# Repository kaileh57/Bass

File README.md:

This is a precision fender-style electric bass designed by me!

It's got three knobs for volume, treble and bass, as well as a custom PCB for active sound managment, and a dual amp system to play audio to EITHER a 1/4" jack OR a standard 3.5mm headphone jack. 
It also has a small rechargable battery to let me play with my headphones away from an amp or power source for hopefully a few hours at a time. 

The bass is pretty standard, and if you wanna 3d print the two parts, buy all the components, the wiring diagram should get you through the complex part!

I made this as I don't currently have an electric bass to play on, and would really like the chance to make my own instrument and start playing new types of music!

Here's what it looks like assembled:

The PCB

Wiring diagram:

The bom can be found in the bom.csv!

This was made (JUST IN TIME) for hack clubs blueprint program, which has been awesome!

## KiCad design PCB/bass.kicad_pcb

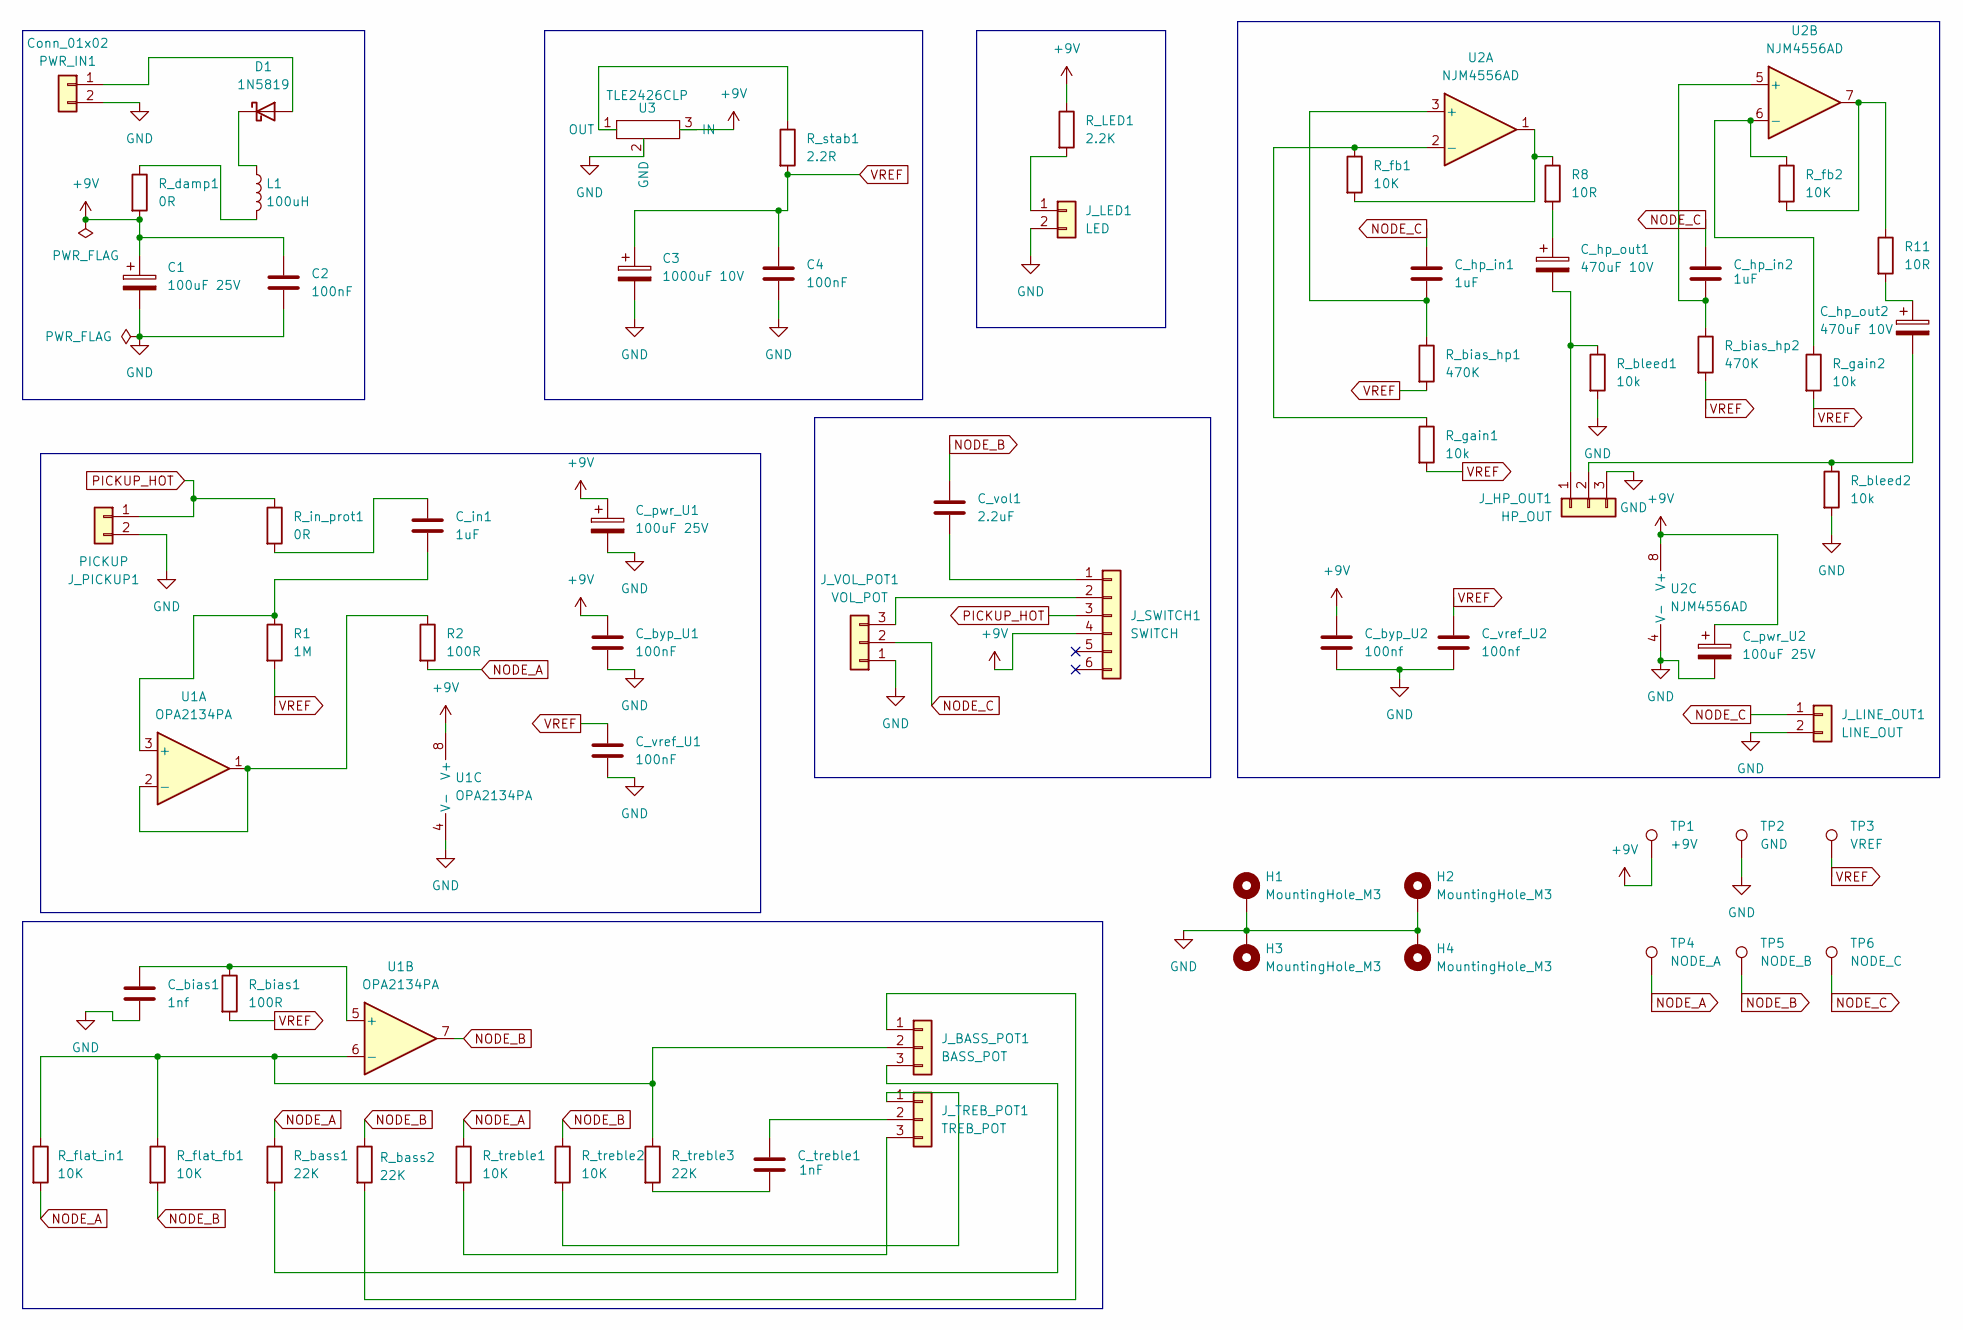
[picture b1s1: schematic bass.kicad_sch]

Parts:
C1: 100uF 25V; CP_Radial_D8.0mm_P3.50mm
C2, C4: 100nF; C_Disc_D5.0mm_W2.5mm_P5.00mm
C3: 1000uF 10V; CP_Radial_D12.5mm_P5.00mm
C_bias1: 1nf; C_Disc_D5.0mm_W2.5mm_P5.00mm
C_byp_U1: 100nF; C_Disc_D5.0mm_W2.5mm_P5.00mm
C_byp_U2: 100nf; C_Disc_D5.0mm_W2.5mm_P5.00mm
C_hp_in1, C_hp_in2: 1uF; C_Rect_L7.2mm_W2.5mm_P5.00mm_FKS2_FKP2_MKS2_MKP2
C_hp_out1, C_hp_out2: 470uF 10V; CP_Radial_D10.0mm_P5.00mm
C_in1: 1uF; C_Rect_L7.2mm_W2.5mm_P5.00mm_FKS2_FKP2_MKS2_MKP2
C_pwr_U1, C_pwr_U2: 100uF 25V; CP_Radial_D8.0mm_P3.50mm
C_treble1: 1nF; C_Rect_L7.2mm_W2.5mm_P5.00mm_FKS2_FKP2_MKS2_MKP2
C_vol1: 2.2uF; C_Rect_L13.5mm_W5.0mm_P10.00mm_FKS3_FKP3_MKS4
C_vref_U1: 100nF; C_Disc_D5.0mm_W2.5mm_P5.00mm
C_vref_U2: 100nf; C_Disc_D5.0mm_W2.5mm_P5.00mm
D1: 1N5819; D_DO-41_SOD81_P10.16mm_Horizontal
H1, H2, H3, H4: MountingHole_M3; MountingHole_3.2mm_M3_Pad
J_BASS_POT1: BASS_POT; PinHeader_1x03_P2.54mm_Vertical
J_HP_OUT1: HP_OUT; PinHeader_1x03_P2.54mm_Vertical
J_LED1: LED; PinHeader_1x02_P2.54mm_Vertical
J_LINE_OUT1: LINE_OUT; PinHeader_1x02_P2.54mm_Vertical
J_PICKUP1: PICKUP; PinHeader_1x02_P2.54mm_Vertical
J_SWITCH1: SWITCH; PinHeader_1x06_P2.54mm_Vertical
J_TREB_POT1: TREB_POT; PinHeader_1x03_P2.54mm_Vertical
J_VOL_POT1: VOL_POT; PinHeader_1x03_P2.54mm_Vertical
L1: 100uH; L_Radial_D10.0mm_P5.00mm_Fastron_07M
PWR_IN1: Conn_01x02; PinHeader_1x02_P2.54mm_Vertical
R1: 1M; R_Axial_DIN0207_L6.3mm_D2.5mm_P10.16mm_Horizontal
R2: 100R; R_Axial_DIN0207_L6.3mm_D2.5mm_P10.16mm_Horizontal
R8, R11: 10R; R_Axial_DIN0207_L6.3mm_D2.5mm_P10.16mm_Horizontal
R_LED1: 2.2K; R_Axial_DIN0207_L6.3mm_D2.5mm_P10.16mm_Horizontal
R_bass1, R_bass2: 22K; R_Axial_DIN0207_L6.3mm_D2.5mm_P10.16mm_Horizontal
R_bias1: 100R; R_Axial_DIN0207_L6.3mm_D2.5mm_P10.16mm_Horizontal
R_bias_hp1, R_bias_hp2: 470K; R_Axial_DIN0207_L6.3mm_D2.5mm_P10.16mm_Horizontal
R_bleed1, R_bleed2: 10k; R_Axial_DIN0207_L6.3mm_D2.5mm_P10.16mm_Horizontal
R_damp1: 0R; R_Axial_DIN0207_L6.3mm_D2.5mm_P10.16mm_Horizontal
R_fb1, R_fb2: 10K; R_Axial_DIN0207_L6.3mm_D2.5mm_P10.16mm_Horizontal
R_flat_fb1: 10K; R_Axial_DIN0207_L6.3mm_D2.5mm_P10.16mm_Horizontal
R_flat_in1: 10K; R_Axial_DIN0207_L6.3mm_D2.5mm_P10.16mm_Horizontal
R_gain1, R_gain2: 10k; R_Axial_DIN0207_L6.3mm_D2.5mm_P10.16mm_Horizontal
R_in_prot1: 0R; R_Axial_DIN0207_L6.3mm_D2.5mm_P10.16mm_Horizontal
R_stab1: 2.2R; R_Axial_DIN0207_L6.3mm_D2.5mm_P10.16mm_Horizontal
R_treble1, R_treble2: 10K; R_Axial_DIN0207_L6.3mm_D2.5mm_P10.16mm_Horizontal
R_treble3: 22K; R_Axial_DIN0207_L6.3mm_D2.5mm_P10.16mm_Horizontal
TP1: +9V; TestPoint_Pad_2.0x2.0mm
TP2: GND; TestPoint_Pad_2.0x2.0mm
TP3: VREF; TestPoint_Pad_2.0x2.0mm
TP4: NODE_A; TestPoint_Pad_2.0x2.0mm
TP5: NODE_B; TestPoint_Pad_2.0x2.0mm
TP6: NODE_C; TestPoint_Pad_2.0x2.0mm
U1: OPA2134PA; DIP-8_W7.62mm
U2: NJM4556AD; DIP-8_W7.62mm
U3: TLE2426CLP; TO-92_Inline

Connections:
+9V: C1.1, C2.1, C_byp_U1.1, C_byp_U2.1, C_pwr_U1.1, C_pwr_U2.1, J_SWITCH1.4, R_LED1.1, R_damp1.2, TP1.1, U1.8 (V+), U2.8 (V+), U3.3 (IN)
GND: C1.2, C2.2, C3.2, C4.2, C_bias1.2, C_byp_U1.2, C_byp_U2.2, C_pwr_U1.2, C_pwr_U2.2, C_vref_U1.2, C_vref_U2.2, H1.1, H2.1, H3.1, H4.1, J_HP_OUT1.3, J_LED1.2, J_LINE_OUT1.2, J_PICKUP1.2, J_VOL_POT1.1, PWR_IN1.2, R_bleed1.2, R_bleed2.2, TP2.1, U1.4 (V-), U2.4 (V-), U3.2 (GND)
NODE_A: R2.2, R_bass1.1, R_flat_in1.2, R_treble1.1, TP4.1
NODE_B: C_vol1.1, R_bass2.1, R_flat_fb1.2, R_treble2.1, TP5.1, U1.7
NODE_C: C_hp_in1.1, C_hp_in2.1, J_LINE_OUT1.1, J_VOL_POT1.2, TP6.1
unnamed: C_hp_out1.1, R8.2
unnamed: C_hp_out2.1, R11.2
unnamed: C_in1.1, R_in_prot1.2
unnamed: C_treble1.2, R_treble3.2
unnamed: D1.2 (A), PWR_IN1.1
unnamed: D1.1 (K), L1.1
unnamed: J_BASS_POT1.1, R_bass2.2
unnamed: J_BASS_POT1.2, R_flat_fb1.1, R_flat_in1.1, R_treble3.1, U1.6 (-)
unnamed: J_BASS_POT1.3, R_bass1.2
unnamed: C_hp_out1.2, J_HP_OUT1.1, R_bleed1.1
unnamed: C_hp_out2.2, J_HP_OUT1.2, R_bleed2.1
unnamed: J_LED1.1, R_LED1.2
unnamed: C_vol1.2, J_SWITCH1.1
unnamed: J_SWITCH1.2, J_VOL_POT1.3
unnamed: J_TREB_POT1.1, R_treble2.2
unnamed: C_treble1.1, J_TREB_POT1.2
unnamed: J_TREB_POT1.3, R_treble1.2
unnamed: L1.2, R_damp1.1
unnamed: R8.1, R_fb1.2, U2.1
unnamed: R11.1, R_fb2.2, U2.7
unnamed: C_in1.2, R1.1, U1.3 (+)
unnamed: R2.1, U1.1, U1.2 (-)
unnamed: C_bias1.1, R_bias1.1, U1.5 (+)
unnamed: C_hp_in1.2, R_bias_hp1.1, U2.3 (+)
unnamed: R_fb1.1, R_gain1.1, U2.2 (-)
unnamed: C_hp_in2.2, R_bias_hp2.1, U2.5 (+)
unnamed: R_fb2.1, R_gain2.1, U2.6 (-)
unnamed: R_stab1.1, U3.1 (OUT)
PICKUP_HOT: J_PICKUP1.1, J_SWITCH1.3, R_in_prot1.1
VREF: C3.1, C4.1, C_vref_U1.1, C_vref_U2.1, R1.2, R_bias1.2, R_bias_hp1.2, R_bias_hp2.2, R_gain1.2, R_gain2.2, R_stab1.2, TP3.1

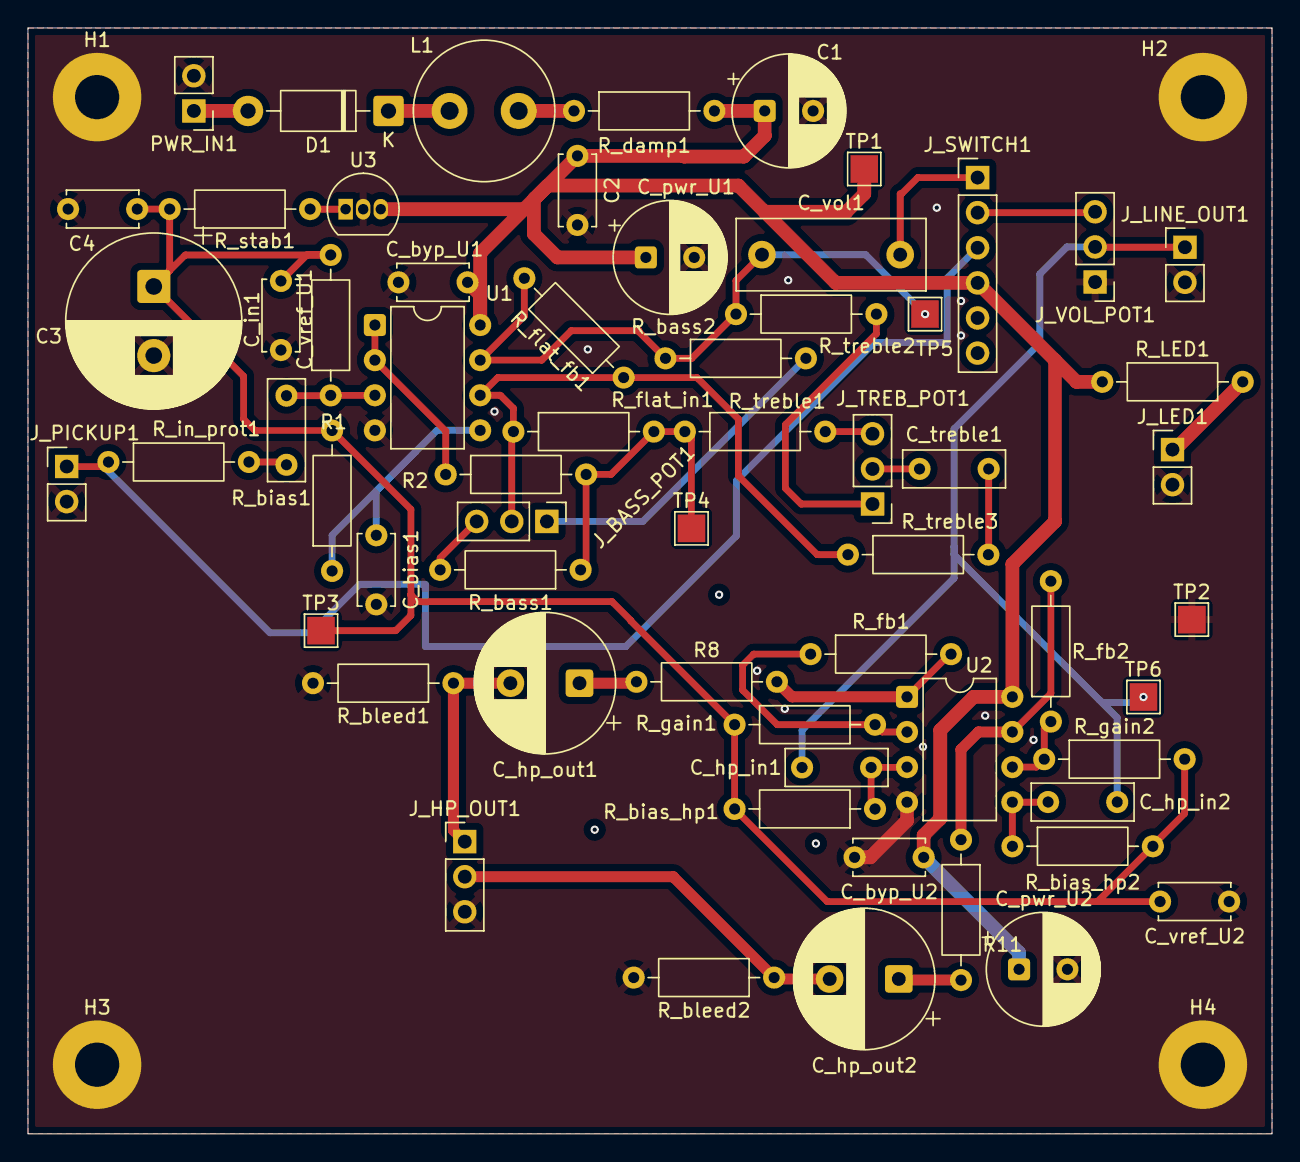
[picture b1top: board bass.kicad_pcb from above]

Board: 2 copper layers, 90.0 x 80.0 mm, 66 parts (0 on the bottom side), 35 nets.

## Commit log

2026-02-22 move all the files into the repo
2026-03-13 progress!
2026-03-15 progresse
2026-03-31 some more work
2026-03-31 remaining project files
2026-03-31 Add wiring diagram to README
    Added wiring diagram image to the README.
2026-04-04 Replace Switchcraft output jack with new model
    Updated the output jack entry in the BOM to a new model and adjusted the price.
2026-04-04 moved headphone jack
